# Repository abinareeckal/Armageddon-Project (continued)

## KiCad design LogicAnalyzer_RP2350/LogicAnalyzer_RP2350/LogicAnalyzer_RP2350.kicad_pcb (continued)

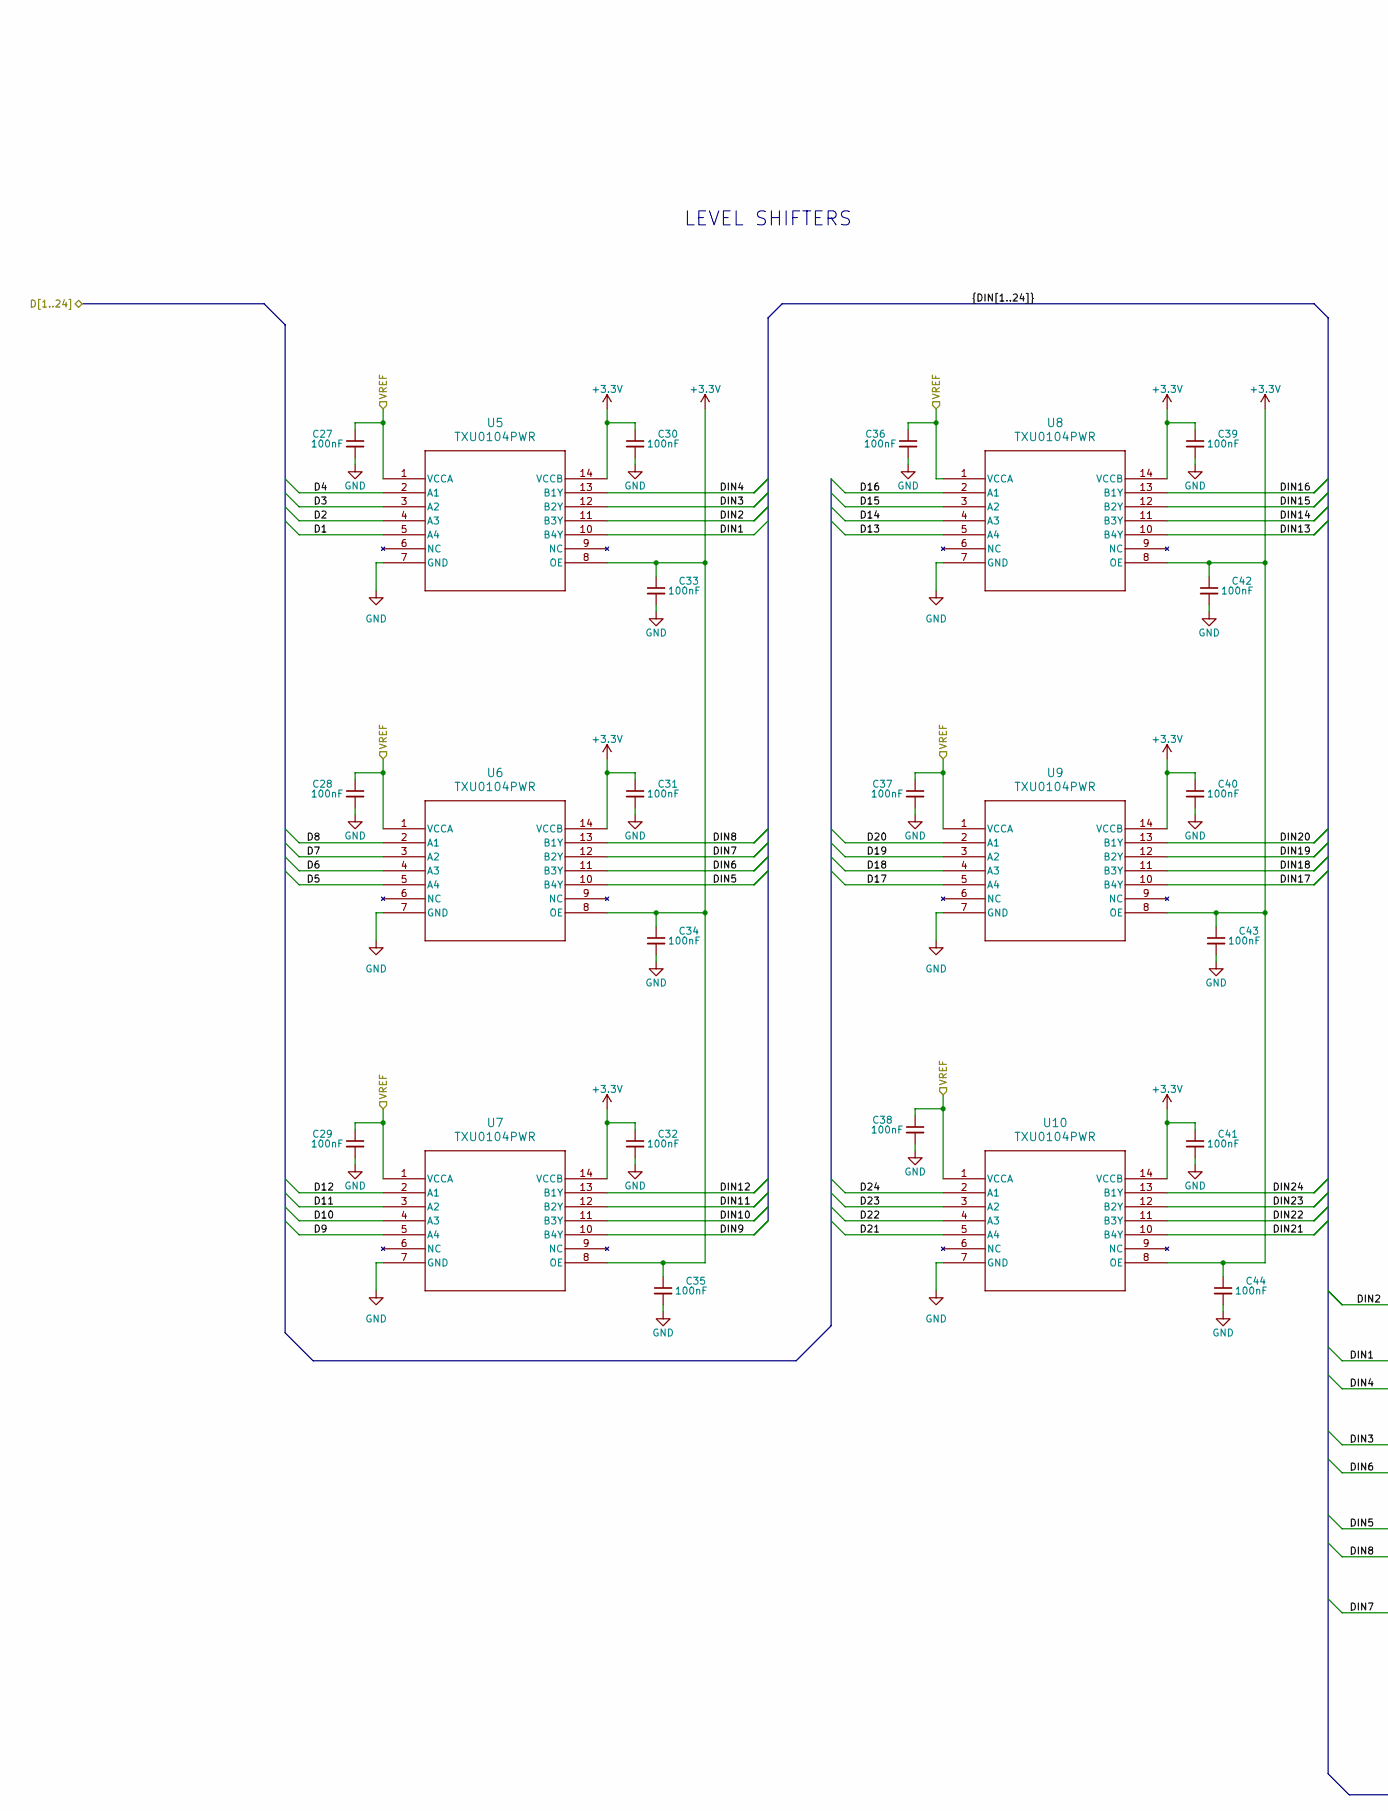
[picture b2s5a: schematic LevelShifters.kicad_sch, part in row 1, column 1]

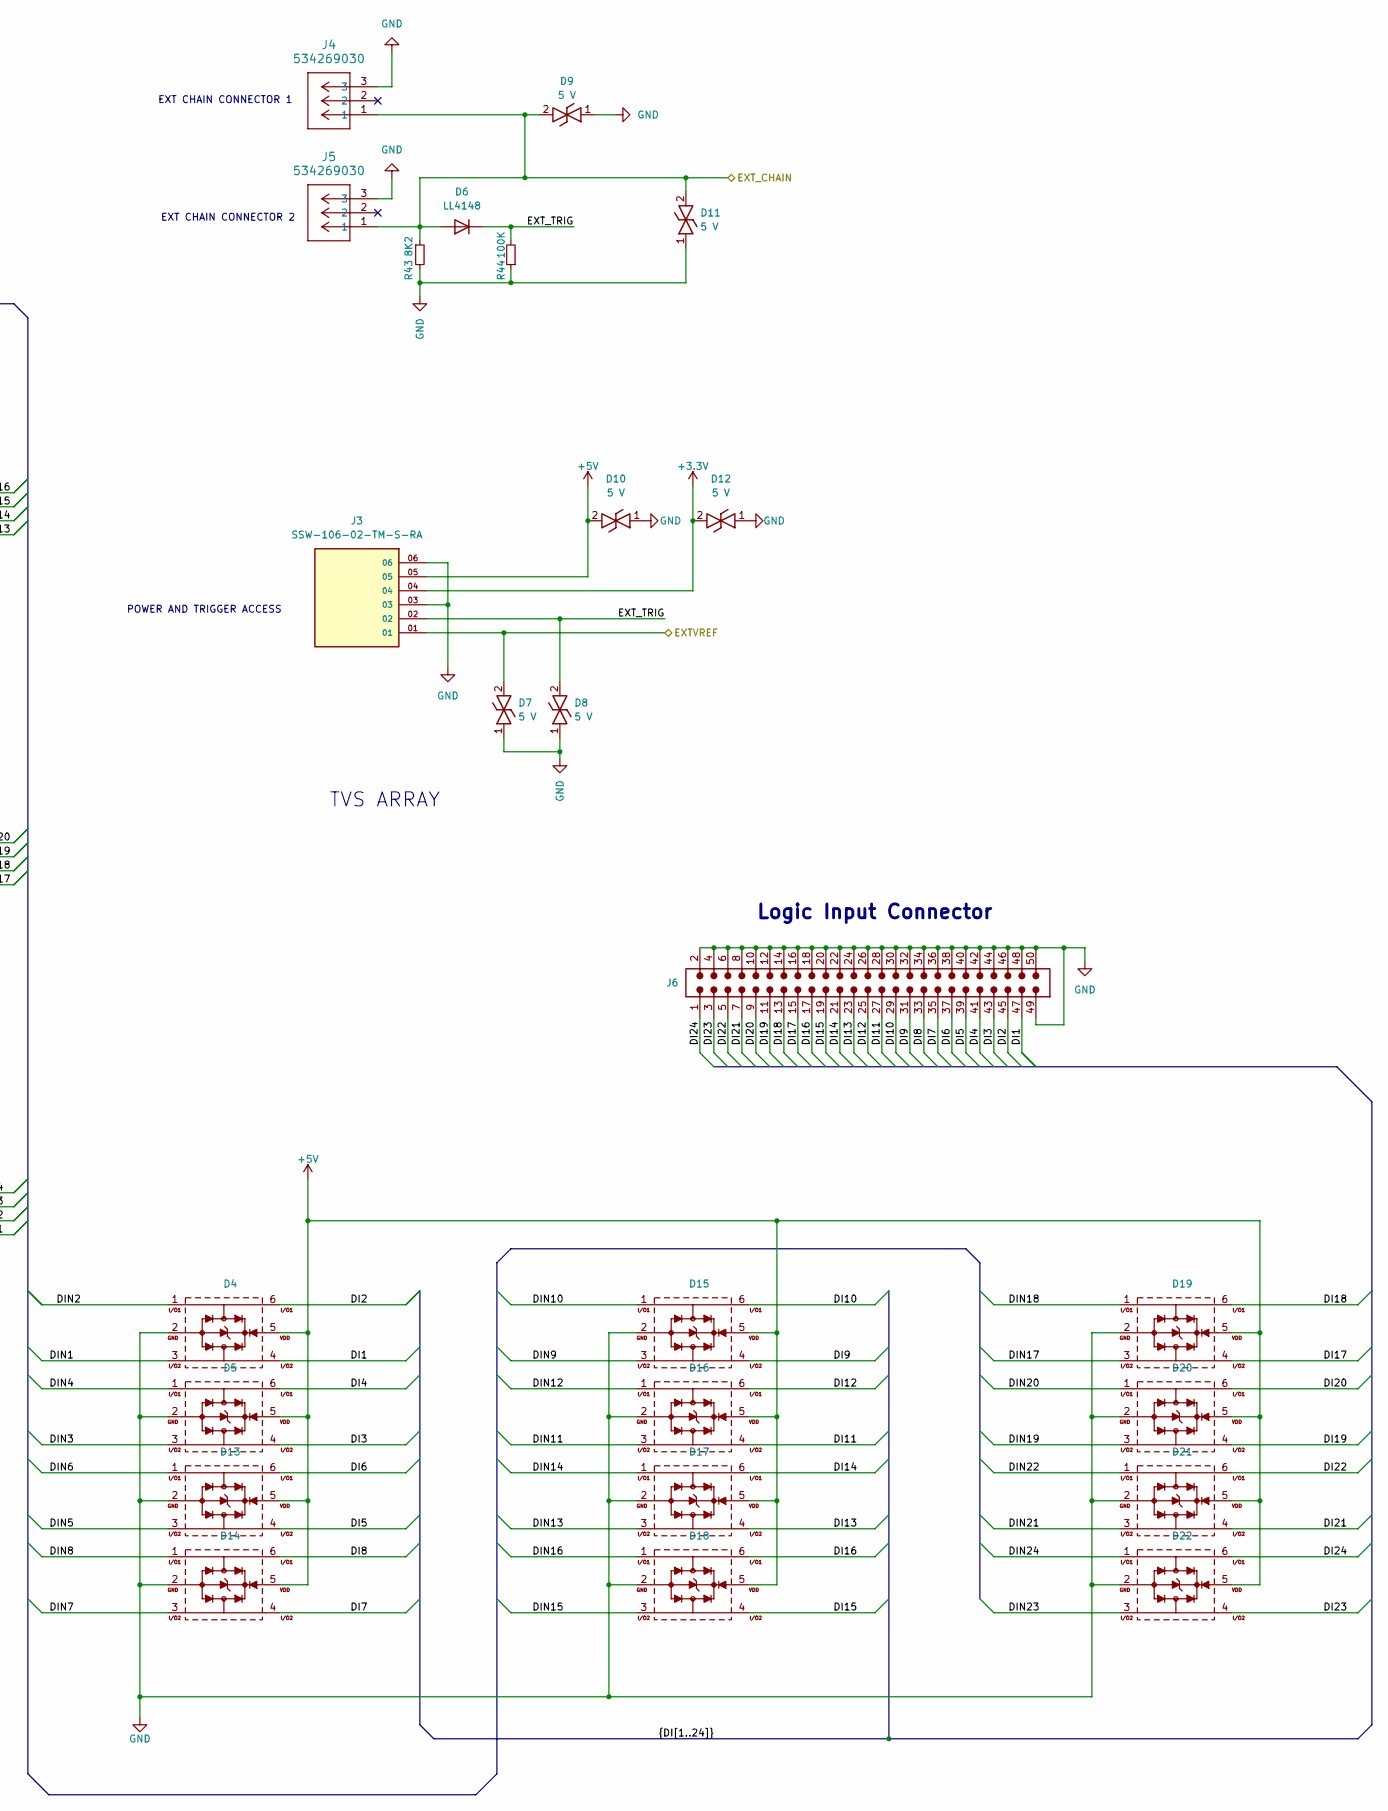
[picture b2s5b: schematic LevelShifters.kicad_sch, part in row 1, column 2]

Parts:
C27, C28, C29, C30, C31, C32, C33, C34, C35, C36, C37, C38, C39, C40, C41, C42, C43, C44: 100nF; C_0603_1608Metric_Pad1.08x0.95mm_HandSolder
D4, D5, D13, D14, D15, D16, D17, D18, D19, D20, D21, D22: SOT563_82400152; D_Wurth_WE-TVS-SOT563; Part Number 82400152
D6: LL4148; D_MiniMELF
D7, D8, D9, D10, D11, D12: 0402_82307050029; D_Wurth_WE-VE-ULC-0402; Part Number 82307050029
J3: SSW-106-02-TM-S-RA; SAMTEC_SSW-106-02-TM-S-RA; PARTREV R
J4, J5: 534269030; CONN03_534269030_MOL
J6: 612050235221; J_Wurth_WR-BHD_612050235221; Working Voltage (V (AC)) 250
R43: 8K2; R_0603_1608Metric_Pad0.98x0.95mm_HandSolder
R44: 100K; R_0603_1608Metric_Pad0.98x0.95mm_HandSolder
U5, U6, U7, U8, U9, U10: TXU0104PWR; TSSOP_0104PWR_TEX

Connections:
+3.3V: C30.1, C31.1, C32.1, C33.1, C34.1, C35.1, C39.1, C40.1, C41.1, C42.1, C43.1, C44.1, D12.2, J3.04, U5.8 (OE), U5.14 (VCCB), U6.8 (OE), U6.14 (VCCB), U7.8 (OE), U7.14 (VCCB), U8.8 (OE), U8.14 (VCCB), U9.8 (OE), U9.14 (VCCB), U10.8 (OE), U10.14 (VCCB); also elsewhere on the board
+5V: D4.5 (VDD), D5.5 (VDD), D10.2, D13.5 (VDD), D14.5 (VDD), D15.5 (VDD), D16.5 (VDD), D17.5 (VDD), D18.5 (VDD), D19.5 (VDD), D20.5 (VDD), D21.5 (VDD), D22.5 (VDD), J3.05; also elsewhere on the board
/FrontPanelInterface/EXTVREF: D7.2, J3.01; also elsewhere on the board
/FrontPanelInterface/VREF: C27.1, C28.1, C29.1, C36.1, C37.1, C38.1, U5.1 (VCCA), U6.1 (VCCA), U7.1 (VCCA), U8.1 (VCCA), U9.1 (VCCA), U10.1 (VCCA); also elsewhere on the board
/LevelShifters/D1: U5.5 (A4); also elsewhere on the board
/LevelShifters/D2: U5.4 (A3); also elsewhere on the board
/LevelShifters/D3: U5.3 (A2); also elsewhere on the board
/LevelShifters/D4: U5.2 (A1); also elsewhere on the board
/LevelShifters/D5: U6.5 (A4); also elsewhere on the board
/LevelShifters/D6: U6.4 (A3); also elsewhere on the board
/LevelShifters/D7: U6.3 (A2); also elsewhere on the board
/LevelShifters/D8: U6.2 (A1); also elsewhere on the board
/LevelShifters/D9: U7.5 (A4); also elsewhere on the board
/LevelShifters/D10: U7.4 (A3); also elsewhere on the board
/LevelShifters/D11: U7.3 (A2); also elsewhere on the board
/LevelShifters/D12: U7.2 (A1); also elsewhere on the board
/LevelShifters/D13: U8.5 (A4); also elsewhere on the board
/LevelShifters/D14: U8.4 (A3); also elsewhere on the board
/LevelShifters/D15: U8.3 (A2); also elsewhere on the board
/LevelShifters/D16: U8.2 (A1); also elsewhere on the board
/LevelShifters/D17: U9.5 (A4); also elsewhere on the board
/LevelShifters/D18: U9.4 (A3); also elsewhere on the board
/LevelShifters/D19: U9.3 (A2); also elsewhere on the board
/LevelShifters/D20: U9.2 (A1); also elsewhere on the board
/LevelShifters/D21: U10.5 (A4); also elsewhere on the board
/LevelShifters/D22: U10.4 (A3); also elsewhere on the board
/LevelShifters/D23: U10.3 (A2); also elsewhere on the board
/LevelShifters/D24: U10.2 (A1); also elsewhere on the board
/LevelShifters/DI1: D4.4 (I/O4), J6.47
/LevelShifters/DI2: D4.6 (I/O3), J6.45
/LevelShifters/DI3: D5.4 (I/O4), J6.43
/LevelShifters/DI4: D5.6 (I/O3), J6.41
/LevelShifters/DI5: D13.4 (I/O4), J6.39
/LevelShifters/DI6: D13.6 (I/O3), J6.37
/LevelShifters/DI7: D14.4 (I/O4), J6.35
/LevelShifters/DI8: D14.6 (I/O3), J6.33
/LevelShifters/DI9: D15.4 (I/O4), J6.31
/LevelShifters/DI10: D15.6 (I/O3), J6.29
/LevelShifters/DI11: D16.4 (I/O4), J6.27
/LevelShifters/DI12: D16.6 (I/O3), J6.25
/LevelShifters/DI13: D17.4 (I/O4), J6.23
/LevelShifters/DI14: D17.6 (I/O3), J6.21
/LevelShifters/DI15: D18.4 (I/O4), J6.19
/LevelShifters/DI16: D18.6 (I/O3), J6.17
/LevelShifters/DI17: D19.4 (I/O4), J6.15
/LevelShifters/DI18: D19.6 (I/O3), J6.13
/LevelShifters/DI19: D20.4 (I/O4), J6.11
/LevelShifters/DI20: D20.6 (I/O3), J6.9
/LevelShifters/DI21: D21.4 (I/O4), J6.7
/LevelShifters/DI22: D21.6 (I/O3), J6.5
/LevelShifters/DI23: D22.4 (I/O4), J6.3
/LevelShifters/DI24: D22.6 (I/O3), J6.1
/LevelShifters/DIN1: D4.3 (I/O2), U5.10 (B4Y)
/LevelShifters/DIN2: D4.1 (I/O1), U5.11 (B3Y)
/LevelShifters/DIN3: D5.3 (I/O2), U5.12 (B2Y)
/LevelShifters/DIN4: D5.1 (I/O1), U5.13 (B1Y)
/LevelShifters/DIN5: D13.3 (I/O2), U6.10 (B4Y)
/LevelShifters/DIN6: D13.1 (I/O1), U6.11 (B3Y)
/LevelShifters/DIN7: D14.3 (I/O2), U6.12 (B2Y)
/LevelShifters/DIN8: D14.1 (I/O1), U6.13 (B1Y)
/LevelShifters/DIN9: D15.3 (I/O2), U7.10 (B4Y)
/LevelShifters/DIN10: D15.1 (I/O1), U7.11 (B3Y)
/LevelShifters/DIN11: D16.3 (I/O2), U7.12 (B2Y)
/LevelShifters/DIN12: D16.1 (I/O1), U7.13 (B1Y)
/LevelShifters/DIN13: D17.3 (I/O2), U8.10 (B4Y)
/LevelShifters/DIN14: D17.1 (I/O1), U8.11 (B3Y)
/LevelShifters/DIN15: D18.3 (I/O2), U8.12 (B2Y)
/LevelShifters/DIN16: D18.1 (I/O1), U8.13 (B1Y)
/LevelShifters/DIN17: D19.3 (I/O2), U9.10 (B4Y)
/LevelShifters/DIN18: D19.1 (I/O1), U9.11 (B3Y)
/LevelShifters/DIN19: D20.3 (I/O2), U9.12 (B2Y)
/LevelShifters/DIN20: D20.1 (I/O1), U9.13 (B1Y)
/LevelShifters/DIN21: D21.3 (I/O2), U10.10 (B4Y)
/LevelShifters/DIN22: D21.1 (I/O1), U10.11 (B3Y)
/LevelShifters/DIN23: D22.3 (I/O2), U10.12 (B2Y)
/LevelShifters/DIN24: D22.1 (I/O1), U10.13 (B1Y)
/LevelShifters/EXT_CHAIN: D6.2 (A), D9.2, D11.2, J4.1, J5.1, R43.1; also elsewhere on the board
/LevelShifters/EXT_TRIG: D6.1 (K), D8.2, J3.02, R44.2
GND: C27.2, C28.2, C29.2, C30.2, C31.2, C32.2, C33.2, C34.2, C35.2, C36.2, C37.2, C38.2, C39.2, C40.2, C41.2, C42.2, C43.2, C44.2, D4.2 (GND), D5.2 (GND), D7.1, D8.1, D9.1, D10.1, D11.1, D12.1, D13.2 (GND), D14.2 (GND), D15.2 (GND), D16.2 (GND), D17.2 (GND), D18.2 (GND), D19.2 (GND), D20.2 (GND), D21.2 (GND), D22.2 (GND), J3.03, J3.06, J4.3, J5.3, J6.2, J6.4, J6.6, J6.8, J6.10, J6.12, J6.14, J6.16, J6.18, J6.20, J6.22, J6.24, J6.26, J6.28, J6.30, J6.32, J6.34, J6.36, J6.38, J6.40, J6.42, J6.44, J6.46, J6.48, J6.49, J6.50, R43.2, R44.1, U5.7 (GND), U6.7 (GND), U7.7 (GND), U8.7 (GND), U9.7 (GND), U10.7 (GND); also elsewhere on the board

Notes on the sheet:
LEVEL SHIFTERS
TVS ARRAY
EXT CHAIN CONNECTOR 2
POWER AND TRIGGER ACCESS
EXT CHAIN CONNECTOR 1
Logic Input Connector

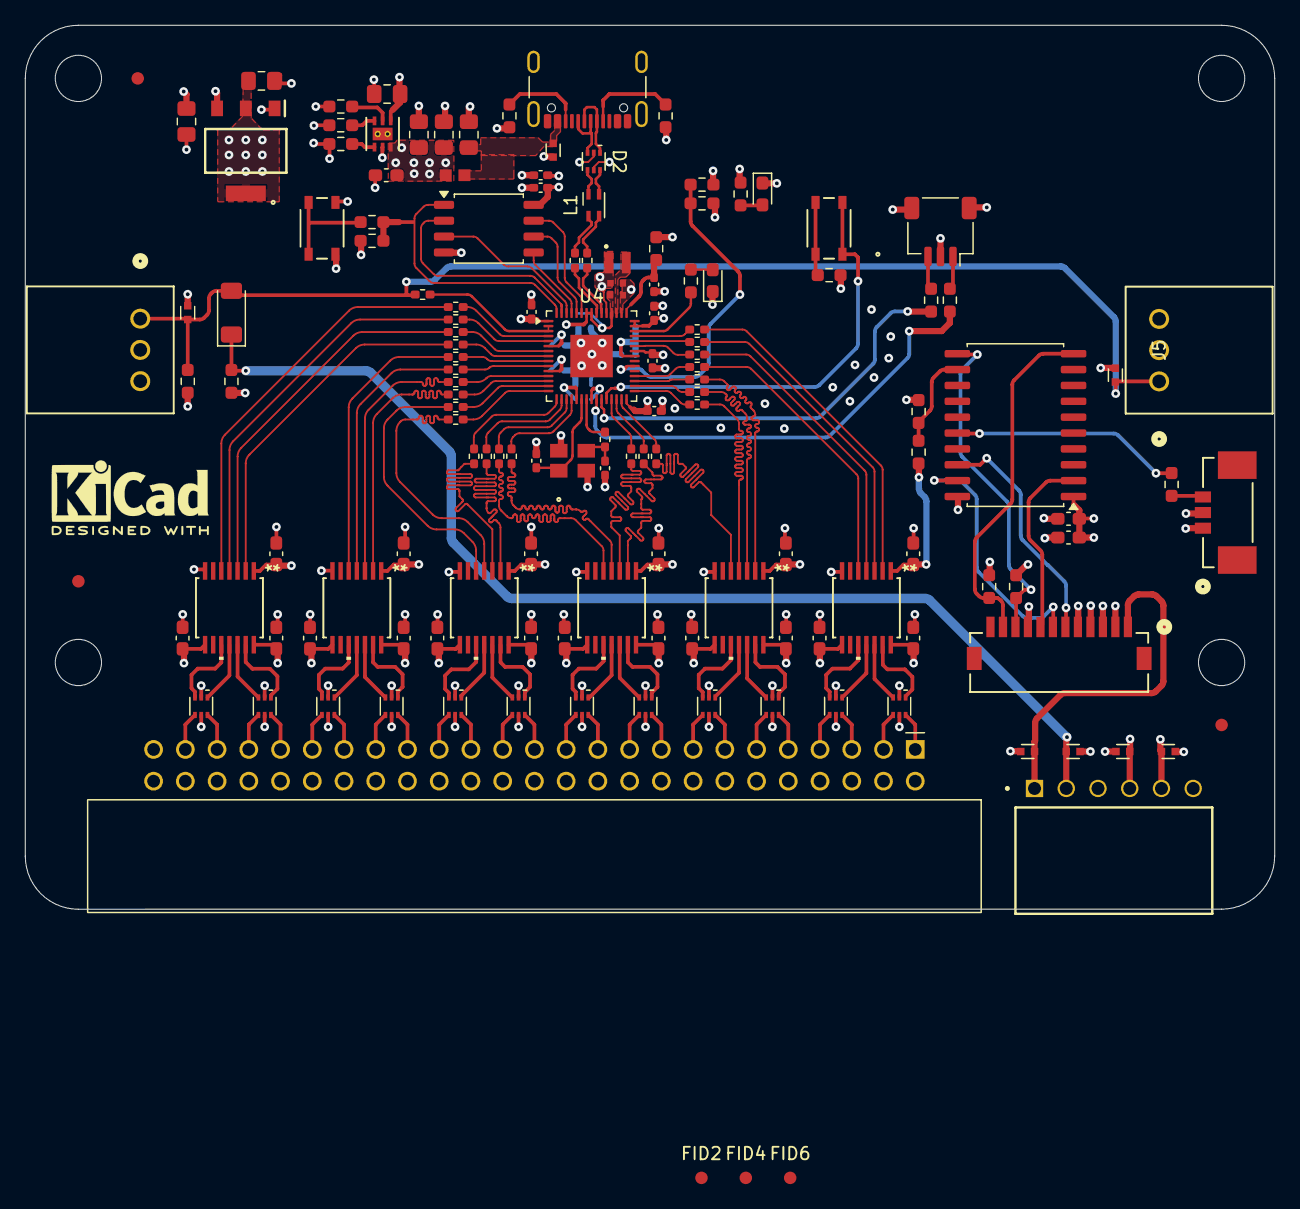
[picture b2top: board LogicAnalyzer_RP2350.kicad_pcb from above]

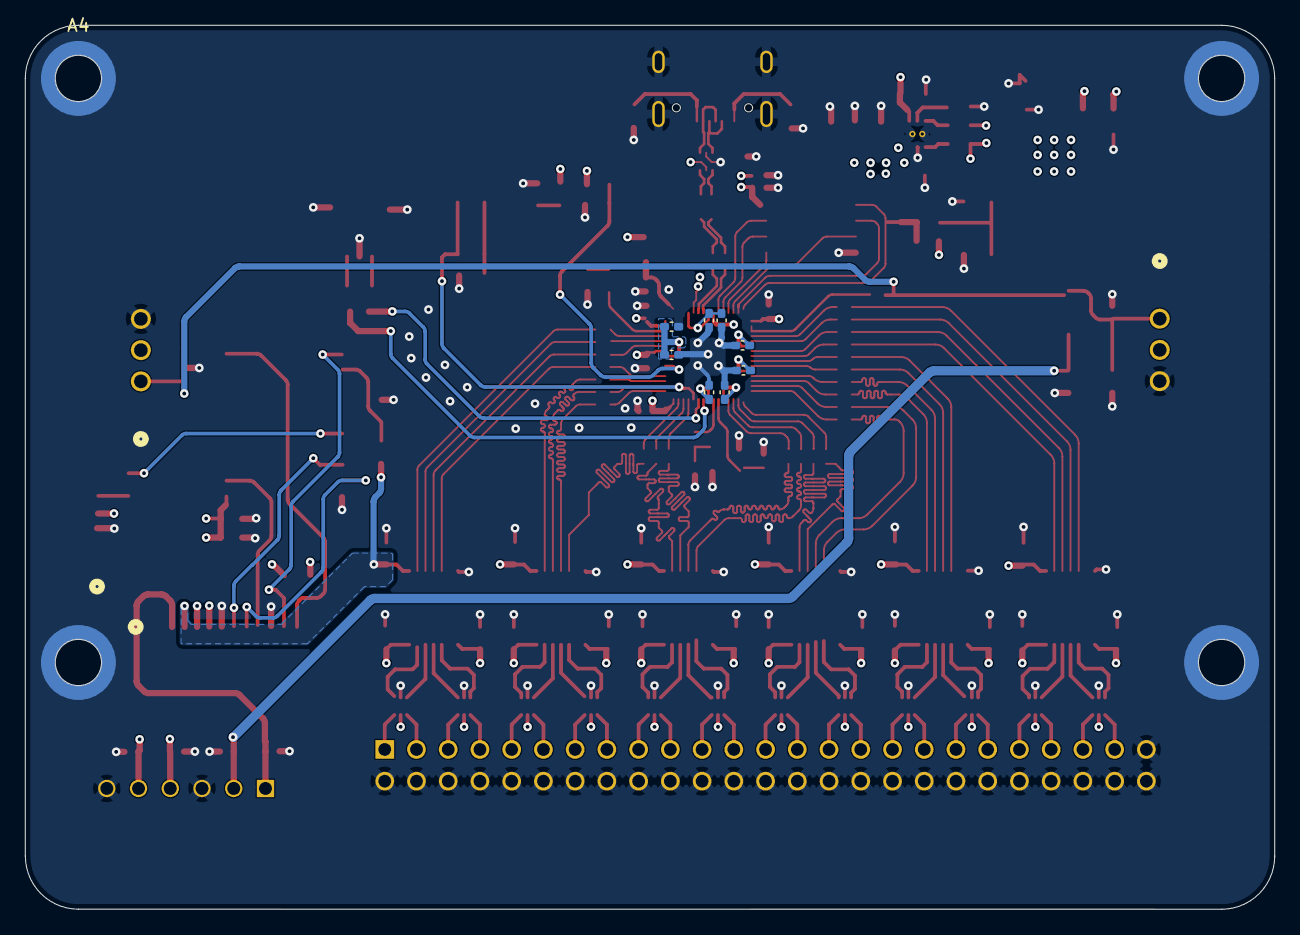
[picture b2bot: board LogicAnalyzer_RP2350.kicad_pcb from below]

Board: 4 copper layers, 100.0 x 70.7 mm, 154 parts (12 on the bottom side), 150 nets.
